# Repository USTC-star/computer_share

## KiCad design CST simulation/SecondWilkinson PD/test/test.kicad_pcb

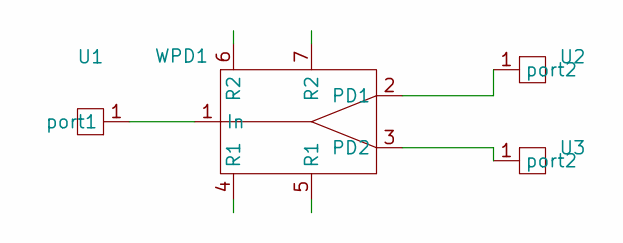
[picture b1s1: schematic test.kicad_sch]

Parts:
U1, U2, U3: WPD_Input_Output_Pad
WPD1: WPD_2Ring_10500_RO4350B_test3

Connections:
unnamed: U1.1 (port1), WPD1.1 (In)
unnamed: U2.1 (port2), WPD1.2 (PD1)
unnamed: U3.1 (port2), WPD1.3 (PD2)

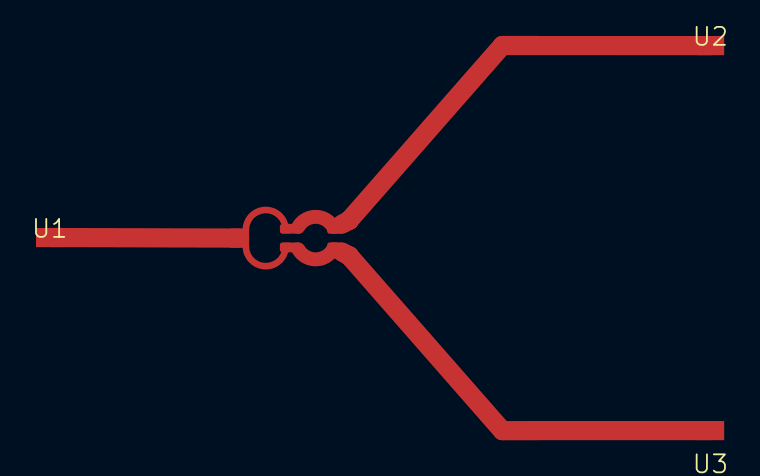
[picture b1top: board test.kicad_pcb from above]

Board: 2 copper layers, 4 parts (0 on the bottom side), 3 nets.

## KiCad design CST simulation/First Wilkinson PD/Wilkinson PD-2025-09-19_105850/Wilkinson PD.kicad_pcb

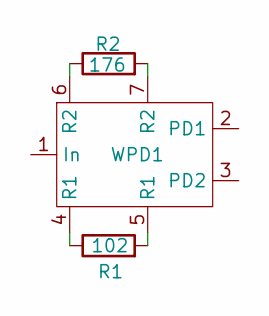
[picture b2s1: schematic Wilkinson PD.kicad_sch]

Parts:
R1: 102; R_0402_1005Metric
R2: 176; R_0402_1005Metric
WPD1: WPD_2Ring_3500

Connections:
unnamed: R1.1, WPD1.4 (R1)
unnamed: R1.2, WPD1.5 (R1)
unnamed: R2.1, WPD1.6 (R2)
unnamed: R2.2, WPD1.7 (R2)

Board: 2 copper layers, 3 parts (0 on the bottom side), 4 nets, no tracks yet.

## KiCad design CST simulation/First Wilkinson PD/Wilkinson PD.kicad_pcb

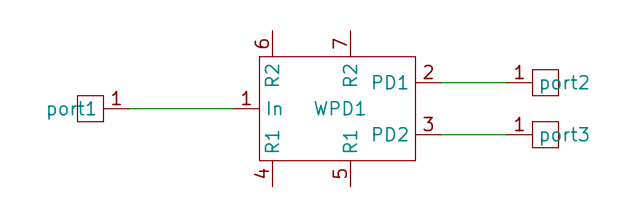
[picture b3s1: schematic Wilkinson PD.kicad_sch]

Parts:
U1, U2, U3: Pad for termination
WPD1: WPD_2Ring_3500

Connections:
unnamed: U1.1 (port3), WPD1.3 (PD2)
unnamed: U2.1 (port2), WPD1.2 (PD1)
unnamed: U3.1 (port1), WPD1.1 (In)

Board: 2 copper layers, 4 parts (0 on the bottom side), 3 nets, no tracks yet.

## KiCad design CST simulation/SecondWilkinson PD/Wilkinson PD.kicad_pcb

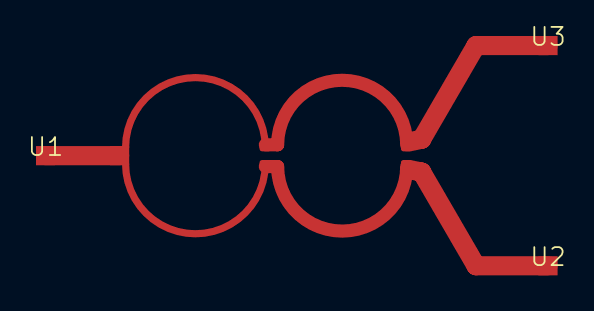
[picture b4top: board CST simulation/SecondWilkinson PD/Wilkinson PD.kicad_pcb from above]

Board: 2 copper layers, 4 parts (0 on the bottom side), 3 nets.

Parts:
U1, U2, U3: Pad for termination
WPD1: WPD_2Ring_3500_RO4350B

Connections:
unnamed: U2.1 (port3), WPD1.3 (PD2)
unnamed: U3.1 (port2), WPD1.2 (PD1)
unnamed: U1.1 (port1), WPD1.1 (In)

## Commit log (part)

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2024-07-18 updata the receier optical calculation
2024-07-18 check the parameters for receiver optical
2024-07-21 new chacters
2024-07-21 delect one page
2024-07-23 updata
2024-07-24 add gr
2024-07-24 modify the ppt
2024-07-24 add book
2024-07-24 add electrodyanmic book
2024-07-25 plus
2024-07-29 add control theory
2024-07-30 reverse process
2024-07-30 code update
2024-07-30 add pdf
2024-08-08 add coupled mode conversion
2024-08-08 modify
2024-08-09 1DFW PPT
2024-08-09 update ppt
2024-08-18 add word of LabVIEW control program
2024-08-18 coupled mode analysis and dissertation
2024-08-18 add brochure
2024-08-18 brochure
2024-08-19 update brochure
2024-08-21 launch optical normal angle
2024-08-23 numerical method
2024-09-03 add 1d fdtd document
2024-09-09 benchmark
2024-09-09 add 1d update
2024-09-22 some update
2024-12-09 new presentation
2024-12-22 paper figure
2024-12-22 none
2024-12-26 new modification after NCL and Yilun
2025-01-01 new modification
2025-01-01 new update
2025-01-02 ipdata
2025-01-02 new updata
2025-01-19 new materials
2025-02-14 new upload
2025-02-17 Test commit
2025-02-17 test
2025-02-18 add new paper
2025-02-18 new+1
2025-02-23 new marerials
2025-02-23 add new DS2019
2025-02-23 new updat
2025-03-30 add paper
2025-03-30 add new
2025-03-30 new paper
2025-03-31 revision
2025-04-15 paper update
2025-04-23 new book
2025-04-29 new results
2025-05-08 new material
2025-05-08 add new tex
2025-05-08 new edition
2025-05-11 after first review
2025-05-11 review
2025-05-22 new cover letter
2025-05-28 manuscript
2025-05-28 new note
2025-06-17 new content
2025-06-21 new paper reference
2025-07-13 new references
2025-07-13 more revision
2025-07-15 push
2025-07-16 new version
2025-07-17 cover letter
2025-08-04 with new updata
2025-09-16 EC paper finish
2025-09-16 add referencce
2025-09-20 add gbr
2025-09-21 new dxf
2025-09-22 add document
2025-09-22 new s
2025-09-23 new model
2025-09-24 new wpd
2025-09-24 desigan notebook
2025-09-24 other boards parameters calculation
2025-09-28 paper reply
2025-09-28 reply to reviewer
2025-09-28 modification laser paper
2025-10-05 WPD 5850
2025-10-05 new components
2025-10-05 gber
2025-10-05 geber
2025-10-06 new part
2025-10-06 new version of 10.5GHz
2025-10-06 finial version
2025-10-07 work introduction
2025-10-09 presentation
2025-10-12 CST UPDATA
2025-10-20 paper
2025-10-22 wpd_test3
2025-10-27 job interview ppt
2025-10-27 job ppt modification
2025-11-12 laser testing
2025-11-13 new file
2025-11-14 uppdate
2025-11-18 add revision note
2025-11-19 new files
2025-11-24 new ade
2025-12-02 revising
2025-12-03 inventory
2025-12-04 letter
2025-12-04 “new”
2025-12-04 new data
2025-12-11 inventory update
2025-12-22 new version of trapping analysis
2026-01-02 new paper ade
2026-01-02 add reference
2026-01-09 new bom
2026-01-13 bom update
2026-01-13 odification
2026-01-19 modify paper
2026-01-19 ade modification
2026-01-19 final version of ade
2026-01-27 ds2019
2026-02-17 new figure
2026-03-09 version.6
2026-03-09 add ref
2026-03-14 reviesion
2026-03-15 add python
2026-03-15 add China CT
2026-03-16 new file CT and MIR
2026-04-01 labor work contract
2026-04-01 new contract
2026-04-06 PLL simulation
2026-05-01 lens code
2026-05-01 gaussian
2026-05-03 figure
2026-05-03 paper work
2026-05-28 add file
2026-05-28 restore the file
